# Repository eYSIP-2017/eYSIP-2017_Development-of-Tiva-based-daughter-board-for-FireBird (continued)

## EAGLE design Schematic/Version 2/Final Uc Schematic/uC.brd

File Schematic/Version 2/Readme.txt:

The version 2 of uC based board is not routed. The sechmatic is changed as per requirement. The components are placed in their respective postions. 
Only the routing part is left.

The version 2 of Plug and Play board is fully completed.

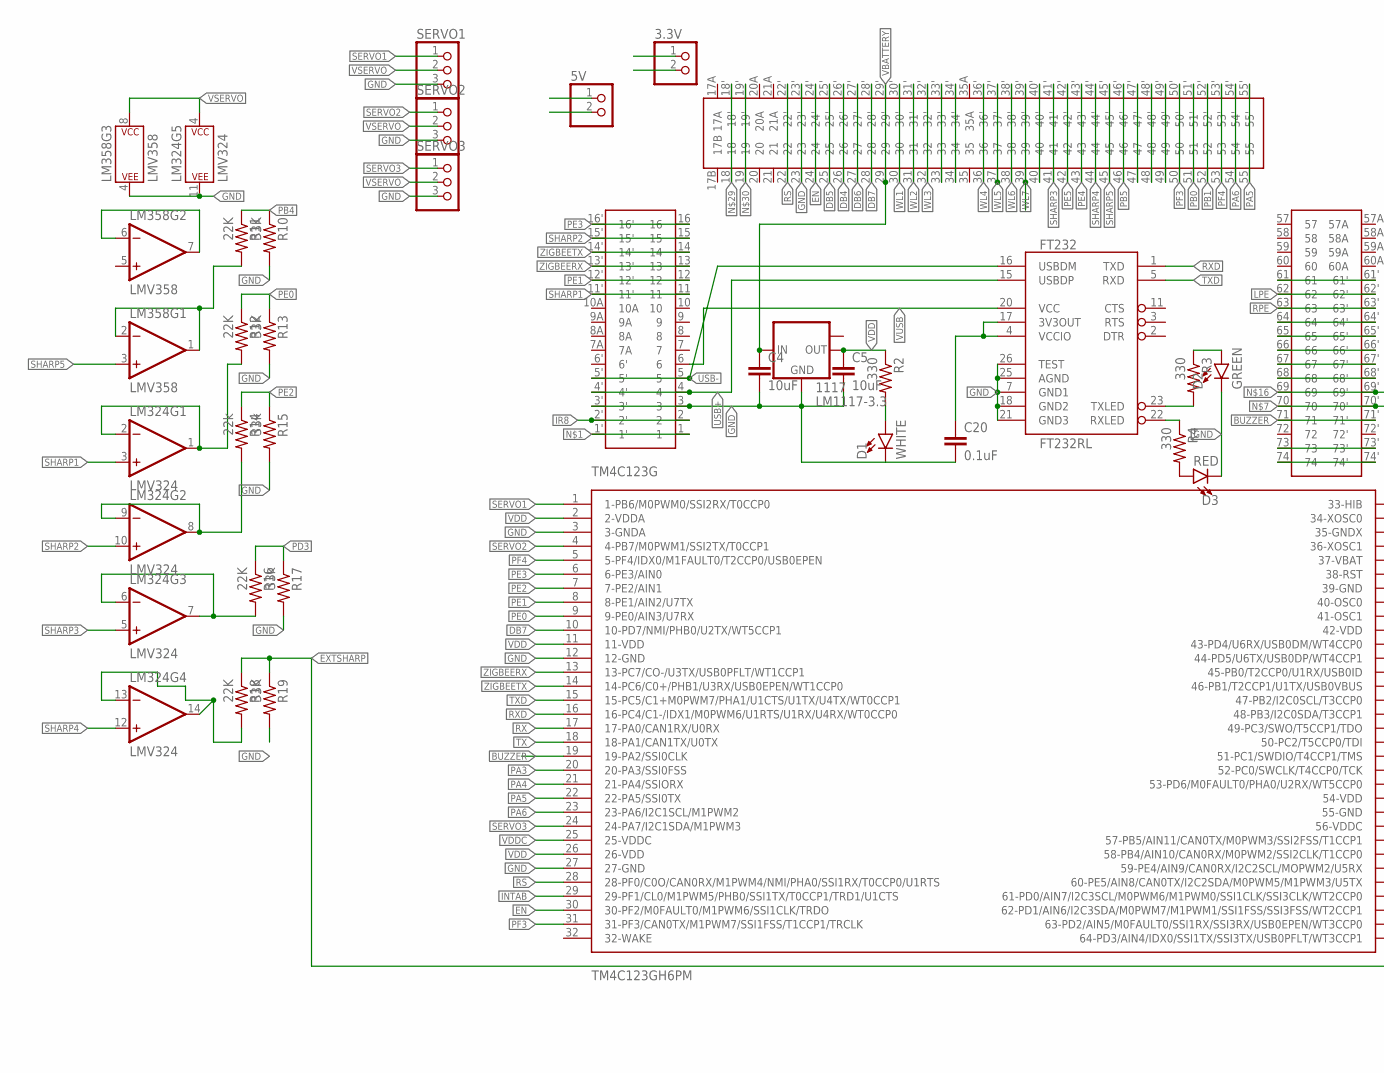
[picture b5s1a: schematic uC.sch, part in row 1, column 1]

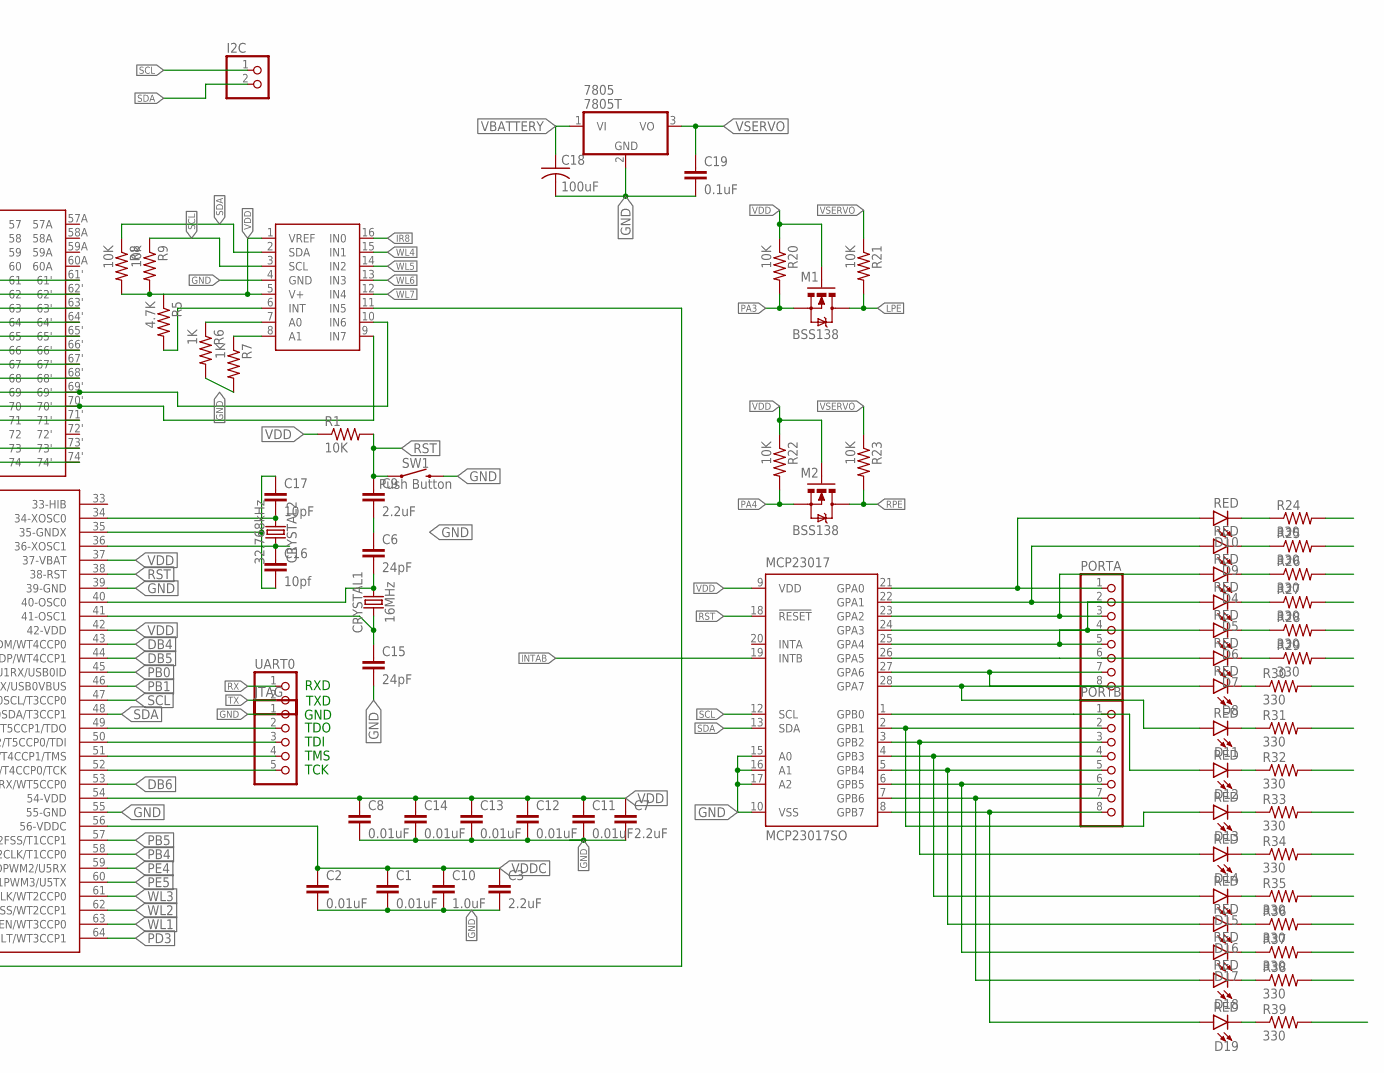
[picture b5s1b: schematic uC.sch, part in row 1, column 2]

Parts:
3.3V, 5V: PINHD-1X2; 1X02
1117: LM1117-3.3; SOT223
7805: 7805T; TO220H
ADC128D818: ADC128D818; ADC12_SD
C1, C2, C8, C11, C12, C13, C14: 0.01uF; 1206
C3, C7, C9: 2.2uF; 1206
C4, C5: 10uF; 1206
C6, C15: 24pF; 1206
C10: 1.0uF; 1206
C16: 10pf; 1206
C17: 10pF; 1206
C18: 100uF; C025-024X044
C19, C20: 0.1uF; 1206
CRYSTAL1: 16MHz; HC49US
CRYSTAL2: 32.768kHz; CRYSTAL-PTH-2X6-CYL
D1: WHITE; LED-1206
D2: GREEN; LED-1206
D3, D4, D5, D6, D7, D8, D9, D10, D11, D12, D13, D14, D15, D16, D17, D18, D19: RED; LED-1206
FT232: FT232RL; SSOP28DB
I2C: PINHD-1X2; 1X02
JTAG: PINHD-1X5_2.54; 1X05
LM324: LMV324; SO14
LM358: LMV358; SO08
M1, M2: BSS138; SOT23-3
MCP23017: MCP23017SO; SO28W
PORTA: PINHD-1X8BIG; 1X08-BIG
PORTB: PINHD-1X8BIG; 1X08-BIG
R1, R8: 10K; M1206
R2, R3, R4, R24, R25, R26, R27, R28, R29, R30, R31, R32, R33, R34, R35, R36, R37, R38, R39: 330; M1206
R5: 4.7K; M1206
R6, R7: 1K; M1206
R9: 10k; M1206
R10, R13, R19: 33K; M1206
R11, R12, R16, R18: 22K; M1206
R14: 22k; M1206
R15, R17: 33k; M1206
R20, R21, R22, R23: 10K; 1206
SERVO1, SERVO2, SERVO3: PINHD-1X3; 1X03
SW1: Push Button; TACTILE_SWITCH_PTH_6.0MM
TM4C123G: TM4C123GH6PM; LQFP
U$1: DAUGHTERBOARDDAUGHTERBOARD; DAUGHTERBOARD
UART0: PINHD-1X2; 1X02

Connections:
BUZZER: TM4C123G.19 (19-PA2/SSI0CLK), U$1.71, U$1.71'
DB4: TM4C123G.43 (43-PD4/U6RX/USB0DM/WT4CCP0), U$1.26, U$1.26'
DB5: TM4C123G.44 (44-PD5/U6TX/USB0DP/WT4CCP1), U$1.25, U$1.25'
DB6: TM4C123G.53 (53-PD6/M0FAULT0/PHA0/U2RX/WT5CCP0), U$1.27, U$1.27'
DB7: TM4C123G.10 (10-PD7/NMI/PHB0/U2TX/WT5CCP1), U$1.28, U$1.28'
EN: TM4C123G.30 (30-PF2/M0FAULT0/M1PWM6/SSI1CLK/TRDO), U$1.24, U$1.24'
EXTSHARP: ADC128D818.11 (IN5), R18.1, R19.1
FDSFSDF: LM324.1 (OUT), LM324.2 (-IN), R12.2
GND: 3.3V.2, 5V.2, 1117.1 (GND), 7805.2 (GND), ADC128D818.4 (GND), C1.2, C2.2, C3.2, C4.2, C5.2, C6.1, C7.2, C8.2, C9.2, C10.2, C11.2, C12.2, C13.2, C14.2, C15.2, C18.2, C19.2, C20.2, D1.C, D2.C, D3.C, FT232.7 (GND1), FT232.18 (GND2), FT232.21 (GND3), FT232.25 (AGND), FT232.26 (TEST), JTAG.1, LM324.11 (P$V-), LM358.4 (P$V-), MCP23017.10 (VSS), MCP23017.15 (A0), MCP23017.16 (A1), MCP23017.17 (A2), R6.2, R7.2, R10.2, R13.2, R15.2, R17.2, R19.2, R24.2, R25.2, R26.2, R27.2, R28.2, R29.2, R30.2, R31.2, R32.2, R33.2, R34.2, R35.2, R36.2, R37.2, R38.2, R39.2, SERVO1.3, SERVO2.3, SERVO3.3, SW1.3 (2), TM4C123G.3 (3-GNDA), TM4C123G.12 (12-GND), TM4C123G.27 (27-GND), TM4C123G.39 (39-GND), TM4C123G.55 (55-GND), U$1.3, U$1.3', U$1.23, U$1.23'
GNDX: C16.2, C17.1, TM4C123G.35 (35-GNDX)
HGHJ: LM358.1 (OUT), LM358.2 (-IN), R11.2
INTAB: MCP23017.19 (INTB), TM4C123G.29 (29-PF1/CL0/M1PWM5/PHB0/SSI1TX/T0CCP1/TR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)
IR8: ADC128D818.16 (IN0), U$1.2, U$1.2'
LPE: M1.3 (D), R21.2, U$1.62, U$1.62'
unnamed: U$1.1, U$1.1'
unnamed: D10.A, MCP23017.21 (GPA0), PORTA.1
unnamed: C6.2, CRYSTAL1.2, TM4C123G.40 (40-OSC0)
unnamed: D9.A, MCP23017.22 (GPA1), PORTA.2
unnamed: LM358.6 (-IN), LM358.7 (OUT)
unnamed: ADC128D818.9 (IN7), U$1.70, U$1.70'
unnamed: D4.A, MCP23017.23 (GPA2), PORTA.3
unnamed: D5.A, MCP23017.24 (GPA3), PORTA.4
unnamed: D6.A, MCP23017.25 (GPA4), PORTA.5
unnamed: JTAG.5, TM4C123G.52 (52-PC0/SWCLK/T4CCP0/TCK)
unnamed: U$1.74, U$1.74'
unnamed: U$1.73, U$1.73'
unnamed: LM324.13 (-IN), LM324.14 (OUT), R18.2
unnamed: JTAG.4, TM4C123G.51 (51-PC1/SWDIO/T4CCP1/TMS)
unnamed: ADC128D818.10 (IN6), D10.C, R24.1, U$1.69, U$1.69'
unnamed: U$1.68, U$1.68'
unnamed: U$1.67, U$1.67'
unnamed: U$1.66, U$1.66'
unnamed: U$1.65, U$1.65'
unnamed: U$1.64, U$1.64'
unnamed: ADC128D818.7 (A0), R6.1
unnamed: D7.A, MCP23017.26 (GPA5), PORTA.6
unnamed: U$1.61, U$1.61'
unnamed: JTAG.3, TM4C123G.50 (50-PC2/T5CCP0/TDI)
unnamed: D1.A, R2.2
unnamed: C17.2, CRYSTAL2.1, TM4C123G.34 (34-XOSC0)
unnamed: C16.1, CRYSTAL2.2, TM4C123G.36 (36-XOSC1)
unnamed: D9.C, R25.1, U$1.18, U$1.18'
unnamed: D4.C, R26.1, U$1.19, U$1.19'
unnamed: JTAG.2, TM4C123G.49 (49-PC3/SWO/T5CCP1/TDO)
unnamed: D8.A, MCP23017.27 (GPA6), PORTA.7
unnamed: D11.A, MCP23017.28 (GPA7), PORTA.8
unnamed: D12.A, MCP23017.1 (GPB0), PORTB.1
unnamed: D13.A, MCP23017.2 (GPB1), PORTB.2
unnamed: D14.A, MCP23017.3 (GPB2), PORTB.3
unnamed: D15.A, MCP23017.4 (GPB3), PORTB.4
unnamed: D16.A, MCP23017.5 (GPB4), PORTB.5
unnamed: D17.A, MCP23017.6 (GPB5), PORTB.6
unnamed: D18.A, MCP23017.7 (GPB6), PORTB.7
unnamed: D19.A, MCP23017.8 (GPB7), PORTB.8
unnamed: U$1.33, U$1.33'
unnamed: U$1.34, U$1.34'
unnamed: D5.C, R27.1
unnamed: D6.C, R28.1
unnamed: D7.C, R29.1
unnamed: D8.C, R30.1
unnamed: U$1.40, U$1.40'
unnamed: D11.C, R31.1
unnamed: D12.C, R32.1
unnamed: D13.C, R33.1
unnamed: D19.C, R39.1
unnamed: D18.C, R38.1
unnamed: D17.C, R37.1
unnamed: U$1.47, U$1.47'
unnamed: U$1.48, U$1.48'
unnamed: U$1.49, U$1.49'
unnamed: D16.C, R36.1
unnamed: D15.C, R35.1
unnamed: D14.C, R34.1
unnamed: FT232.22 (RXLED), R4.1
unnamed: FT232.23 (TXLED), R3.2
unnamed: D3.A, R4.2
unnamed: D2.A, R3.1
unnamed: ADC128D818.6 (INT), R5.2
unnamed: ADC128D818.8 (A1), R7.1
unnamed: C20.1, FT232.4 (VCCIO), FT232.17 (3V3OUT)
NO: C15.1, CRYSTAL1.1, TM4C123G.41 (41-OSC1)
PA3: M1.2 (S), R20.2, TM4C123G.20 (20-PA3/SSI0FSS)
PA4: M2.2 (S), R22.2, TM4C123G.21 (21-PA4/SSIORX)
PA5: TM4C123G.22 (22-PA5/SSI0TX), U$1.55, U$1.55'
PA6: TM4C123G.23 (23-PA6/I2C1SCL/M1PWM2), U$1.54, U$1.54'
PB0: TM4C123G.45 (45-PB0/T2CCP0/U1RX/USB0ID), U$1.51, U$1.51'
PB1: TM4C123G.46 (46-PB1/T2CCP1/U1TX/USB0VBUS), U$1.52, U$1.52'
PB4: R10.1, R11.1, TM4C123G.58 (58-PB4/AIN10/CAN0RX/M0PWM2/SSI2CLK/T1CC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)
PB5: TM4C123G.57 (57-PB5/AIN11/CAN0TX/M0PWM3/SSI2FSS/T1CC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), U$1.46, U$1.46'
PD3: R16.1, R17.1, TM4C123G.64 (64-PD3/AIN4/IDX0/SSI1TX/SSI3TX/USB0PFLT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)
PE0: R12.1, R13.1, TM4C123G.9 (9-PE0/AIN3/U7RX)
PE1: TM4C123G.8 (8-PE1/AIN2/U7TX), U$1.12, U$1.12'
PE2: R14.1, R15.1, TM4C123G.7 (7-PE2/AIN1)
PE3: TM4C123G.6 (6-PE3/AIN0), U$1.16, U$1.16'
PE4: TM4C123G.59 (59-PE4/AIN9/CAN0RX/I2C2SCL/MOPWM2/U5RX), U$1.43, U$1.43'
PE5: TM4C123G.60 (60-PE5/AIN8/CAN0TX/I2C2SDA/M0PWM5/M1PWM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), U$1.42, U$1.42'
PF3: TM4C123G.31 (31-PF3/CAN0TX/M1PWM7/SSI1FSS/T1CCP1/TRC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), U$1.50, U$1.50'
PF4: TM4C123G.5 (5-PF4/IDX0/M1FAULT0/T2CCP0/USB0EPEN), U$1.53, U$1.53'
RPE: M2.3 (D), R23.2, U$1.63, U$1.63'
RS: TM4C123G.28 (28-PF0/C0O/CAN0RX/M1PWM4/NMI/PHA0/SSI1R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), U$1.22, U$1.22'
RST: C9.1, MCP23017.18 (!RESET), R1.2, SW1.1, TM4C123G.38 (38-RST)
RX: TM4C123G.17 (17-PA0/CAN1RX/U0RX), UART0.1
RXD: FT232.1 (TXD), TM4C123G.16 (16-PC4/C1-/IDX1/M0PWM6/U1RTS/U1RX/U4RX/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)
SCL: ADC128D818.3 (SCL), I2C.1, MCP23017.12 (SCL), R9.1, TM4C123G.47 (47-PB2/I2C0SCL/T3CCP0)
SDA: ADC128D818.2 (SDA), I2C.2, MCP23017.13 (SDA), R8.1, TM4C123G.48 (48-PB3/I2C0SDA/T3CCP1)
SDFSDFSD: LM324.8 (OUT), LM324.9 (-IN), R14.2
SERVO1: SERVO1.1, TM4C123G.1 (1-PB6/M0PWM0/SSI2RX/T0CCP0)
SERVO2: SERVO2.1, TM4C123G.4 (4-PB7/M0PWM1/SSI2TX/T0CCP1)
SERVO3: SERVO3.1, TM4C123G.24 (24-PA7/I2C1SDA/M1PWM3)
SHARP1: LM324.3 (+IN), U$1.11, U$1.11'
SHARP2: LM324.10 (+IN), U$1.15, U$1.15'
SHARP3: LM324.5 (+IN), U$1.41, U$1.41'
SHARP4: LM324.12 (+IN), U$1.44, U$1.44'
SHARP5: LM358.3 (+IN), U$1.45, U$1.45'
TX: TM4C123G.18 (18-PA1/CAN1TX/U0TX), UART0.2
TXD: FT232.5 (RXD), TM4C123G.15 (15-PC5/C1+M0PWM7/PHA1/U1CTS/U1TX/U4TX/W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)
USB+: FT232.15 (USBDP), U$1.4, U$1.4'
USB-: FT232.16 (USBDM), U$1.5, U$1.5'
VBATTERY: 1117.3 (IN), 7805.1 (VI), C4.1, C18.1, U$1.29, U$1.29'
VDD: 3.3V.1, 1117.2 (OUT), ADC128D818.1 (VREF), ADC128D818.5 (V+), C5.1, C7.1, C8.1, C11.1, C12.1, C13.1, C14.1, M1.1 (G), M2.1 (G), MCP23017.9 (VDD), R1.1, R2.1, R5.1, R8.2, R9.2, R20.1, R22.1, TM4C123G.2 (2-VDDA), TM4C123G.11 (11-VDD), TM4C123G.26 (26-VDD), TM4C123G.37 (37-VBAT), TM4C123G.42 (42-VDD), TM4C123G.54 (54-VDD)
VDDC: C1.1, C2.1, C3.1, C10.1, TM4C123G.25 (25-VDDC), TM4C123G.56 (56-VDDC)
VSERVO: 5V.1, 7805.3 (VO), C19.1, LM324.4 (P$V+), LM358.8 (P$V+), R21.1, R23.1, SERVO1.2, SERVO2.2, SERVO3.2
VUSB: FT232.20 (VCC), U$1.6
WL1: TM4C123G.63 (63-PD2/AIN5/M0FAULT0/SSI1RX/SSI3RX/USB0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), U$1.30, U$1.30'
WL2: TM4C123G.62 (62-PD1/AIN6/I2C3SDA/M0PWM7/M1PWM1/SSI1F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), U$1.31, U$1.31'
WL3: TM4C123G.61 (61-PD0/AIN7/I2C3SCL/M0PWM6/M1PWM0/SSI1C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), U$1.32, U$1.32'
WL4: ADC128D818.15 (IN1), U$1.36, U$1.36'
WL5: ADC128D818.14 (IN2), U$1.37, U$1.37'
WL6: ADC128D818.13 (IN3), U$1.38, U$1.38'
WL7: ADC128D818.12 (IN4), U$1.39, U$1.39'
XXVX: LM324.6 (-IN), LM324.7 (OUT), R16.2
ZIGBEERX: TM4C123G.13 (13-PC7/CO-/U3TX/USB0PFLT/WT1CCP1), U$1.13, U$1.13'
ZIGBEETX: TM4C123G.14 (14-PC6/C0+/PHB1/U3RX/USB0EPEN/WT1CCP0), U$1.14, U$1.14'

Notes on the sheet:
TCK
TMS
TDI
TDO
TXD
RXD
GND

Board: 2 copper layers, 102 parts (37 on the bottom side), 133 nets, no tracks yet.

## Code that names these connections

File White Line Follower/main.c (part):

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
ADC Connection:
          CH       PORT    Sensor
           2       PE1     White line sensor 3
           1       PE2     White line sensor 2
           0       PE3     White line sensor 1
          11       PB5     IR Proximity analog sensor 1
           7       PD5     IR Proximity analog sensor 2
           4       PD3     IR Proximity analog sensor 3
           6       PD1     IR Proximity analog sensor 4
           8       PE5     IR Proximity analog sensor 5
           3       PE0     IR Proximity analog sensor 7
          10       PB4     Sharp IR range sensor 1
           5       PD2     Sharp IR range sensor 3
           9       PE4     Sharp IR range sensor 5
LCD Connection:
             LCD      Board Pins
              RS  --> PD6
              RW  --> GND
              EN  --> PD7
              DB7 --> PA5
              DB6 --> PA4
              DB5 --> PA3
              DB4 --> PA2
Motor Connection:
                L-1---->PF3;        L-2---->PB3;
                R-1---->PC4;        R-2---->PC6;
                PF2----> PWM L     PC5----> PWM R;

****************************************************************************************************/
#include <stdint.h>
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 * Macros have been defined at starting
 * Macros for directions are 8 bits
 * Out of these 8 bits only 4 are used
 * Bit 0 (LSB) corresponds to PB3
 * Bit 3       corresponds to PF3
 * Bit 4       corresponds to PC4
 * Bit 6       corresponds to PF6
 *****************************************************/
void motion(uint8_t direction){
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
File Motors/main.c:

/********************************************************************************
 Written by: Ayush Gaurav

 Date: 29th May 2017

This experiment demonstrates simple motion control.

 Concepts covered: Simple motion control

 There are two components to the motion control:
 1. Direction control using pins PORTA0 to PORTA3
 2. Velocity control by PWM on pins PA4 and PA5 using OC5A and OC5B of timer 5.

 In this experiment for the simplicity PL3 and PL4 are kept at logic 1.

 Pins for PWM are kept at logic 1.

 Connection Details:    L-1---->PB0;        L-2---->PB1;
                        R-1---->PB2;        R-2---->PB3;
                        PB4 ----> PWM L  PB5----> PWM R;


*********************************************************************************/
#include <stdint.h>
#include <stdbool.h>
#include "inc/hw_types.h"
#include "inc/hw_memmap.h"
//This header File is important to Unlock GPIO Pins
#include "inc/hw_gpio.h"
#include "driverlib/sysctl.h"
#include "driverlib/gpio.h"
#define motorPort       GPIO_PORTB_BASE
#define leftMotor1      GPIO_PIN_0
#define leftMotor2      GPIO_PIN_1
#define leftMotorPWM    GPIO_PIN_4
#define rightMotor1     GPIO_PIN_2
#define rightMotor2     GPIO_PIN_3
#define rightMotorPWM   GPIO_PIN_5
#define right           0x3A
#define left            0x35
#define forward         0x36
#define backward        0x39
#define stop            0x30
void setupCLK();
void peripheralEnable();
void configIOPin();
void delay_ms(uint64_t delay);
void delay_ms(uint64_t delay);
void motion(uint8_t);
int main(void) {
    setupCLK();
    peripheralEnable();
    configIOPin();
    while(1){
        motion(forward);
        delay_ms(1000);
        motion(right);
        delay_ms(1000);
        motion(left);
        delay_ms(1000);
        motion(backward);
        delay_ms(1000);
    }
}
/***************************************************************************************
 * This function is used to setup Clock frequency of the controller
 * It can be changed through codes
 * In this we have set frequency as 40Mhz
 * Frequency is set by SYSDIV which can be found in data sheet for different frequencies
 ***************************************************************************************/
void setupCLK(){
    SysCtlClockSet(SYSCTL_SYSDIV_5|SYSCTL_USE_PLL|SYSCTL_XTAL_16MHZ|SYSCTL_OSC_MAIN);
}
/*******************************
 * Enabling System Peripherals
 * PORTF in this case
 * PF1 for buzzer output
 ******************************/
void peripheralEnable(){
    SysCtlPeripheralEnable(SYSCTL_PERIPH_GPIOB);
}
/*************************************
 * Configuring Pin as Input Or Output
 *************************************/
void configIOPin(){
    GPIOPinTypeGPIOOutput(motorPort,rightMotor1|rightMotor2|rightMotorPWM|leftMotorPWM|leftMotor1|leftMotor2);
}
/*************************************
 * Calculating Delays
 *************************************/
void delay_ms(uint64_t delay){
    SysCtlDelay(delay*(SysCtlClockGet()/3000));
}
void delay_us(uint64_t delay){
    SysCtlDelay(delay*(SysCtlClockGet()/3000000UL));
}
void motion(uint8_t direction){
    GPIOPinWrite(motorPort,rightMotor1|rightMotor2|rightMotorPWM|leftMotorPWM|leftMotor1|leftMotor2,direction);
}

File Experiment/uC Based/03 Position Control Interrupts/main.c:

/*********************************************************************************
 Written by: Ayush Gaurav and Nagesh K.
From ERTS Lab, CSE Department, IIT Bombay.

 Date: 16th June 2017

 This experiment demonstrates use of position encoders present on both the wheels.

 Concepts covered: External Interrupts, Position control

 Microcontroller pins used:
 L-1---->PB0;        L-2---->PB1;
 R-1---->PF4;        R-2---->PA5;
 PF3----> PWM L     PA6----> PWM R;
 PA4 : External interrupt for left motor position encoder
 PA3 : External interrupt for the right position encoder
**********************************************************************************/

#include <stdint.h>
#include <stdbool.h>
#include "inc/tm4c123gh6pm.h"
#include "inc/hw_memmap.h"
#include "inc/hw_types.h"
#include "inc/hw_gpio.h"
#include "driverlib/sysctl.h"
#include "driverlib/interrupt.h"
#include "driverlib/gpio.h"
#define right           0x22
#define left            0x11
#define softRight       0x02
#define softLeft        0x10
#define forward         0x12
#define backward        0x21
#define stop            0x00
void setupCLK();
void peripheralEnable();
void gpioEnable();
void interruptEnable();
void encoderInterruptEncountered();
void linearDistanceMM(unsigned int);
void angleRotate(uint16_t);
void forwardMM(unsigned int);
void backwardMM(unsigned int);
void leftDegrees(unsigned int);
void rightDegrees(unsigned int);
void delay_ms(uint64_t delay);
void delay_us(uint64_t delay);
void motion(uint8_t direction);
volatile uint16_t ShaftCountRight=0,ShaftCountLeft=0;
int main(void) {
    setupCLK();
    peripheralEnable();
    gpioEnable();
    interruptEnable();
    while(1){
        forwardMM(100);
        delay_ms(1000);
        rightDegrees(90);
        delay_ms(1000);
}
}

/***************************************************************************************
 * This function is used to setup Clock frequency of the controller
 * It can be changed through codes
 * In this we have set frequency as 40Mhz
 * Frequency is set by SYSDIV which can be found in data sheet for different frequencies
 ***************************************************************************************/
void setupCLK(){
    SysCtlClockSet(SYSCTL_SYSDIV_5|SYSCTL_USE_PLL|SYSCTL_XTAL_16MHZ|SYSCTL_OSC_MAIN);
}

/*******************************
 * Enabling System Peripherals
 * PORTF,PORTB and PORTA in this case
 ******************************/
void peripheralEnable(){
    SysCtlPeripheralEnable(SYSCTL_PERIPH_GPIOB);
    SysCtlPeripheralEnable(SYSCTL_PERIPH_GPIOF);
    SysCtlPeripheralEnable(SYSCTL_PERIPH_GPIOA);
}

/*************************************
 * Configuring Pin as Input Or Output
 * Setting PWM Pins to Always High
 * Weak Pull to the Input Pins
 *************************************/
void gpioEnable(){
    GPIOPinTypeGPIOOutput(GPIO_PORTF_BASE,GPIO_PIN_1|GPIO_PIN_2);
    GPIOPinTypeGPIOOutput(GPIO_PORTB_BASE,GPIO_PIN_0|GPIO_PIN_1);
    GPIOPinTypeGPIOOutput(GPIO_PORTA_BASE,GPIO_PIN_6|GPIO_PIN_5);
    GPIOPinTypeGPIOOutput(GPIO_PORTF_BASE,GPIO_PIN_4|GPIO_PIN_3);
    GPIOPinWrite(GPIO_PORTF_BASE,GPIO_PIN_3,255);
    GPIOPinWrite(GPIO_PORTA_BASE,GPIO_PIN_6,255);
    GPIOPinTypeGPIOInput(GPIO_PORTA_BASE, GPIO_PIN_4|GPIO_PIN_3);
    GPIOPadConfigSet(GPIO_PORTA_BASE ,GPIO_PIN_4|GPIO_PIN_5,GPIO_STRENGTH_2MA,GPIO_PIN_TYPE_STD_WPU);
}
/****For Enabling Interrupt on PortA****/
void interruptEnable(){
    GPIOIntDisable(GPIO_PORTA_BASE,GPIO_PIN_4|GPIO_PIN_3);
    GPIOIntClear(GPIO_PORTA_BASE, GPIO_PIN_4|GPIO_PIN_3);
    GPIOIntRegister(GPIO_PORTA_BASE, encoderInterruptEncountered);
    GPIOIntTypeSet(GPIO_PORTA_BASE,GPIO_PIN_4|GPIO_PIN_3,GPIO_FALLING_EDGE);
    GPIOIntEnable(GPIO_PORTA_BASE,GPIO_PIN_4|GPIO_PIN_3);
}
/**** ISR For External Interrupt on PortA************************
 * Check on which pin of the PORTA has encountered an interrupt
 * There is only one ISR for complete PORT
 * No two PORTs can have same ISR
 ****************************************************************/
void encoderInterruptEncountered(){
   if(GPIOIntStatus(GPIO_PORTA_BASE, false)&GPIO_PIN_4){
       ShaftCountLeft++;
       GPIOIntClear(GPIO_PORTA_BASE, GPIO_PIN_4);
   }
   if(GPIOIntStatus(GPIO_PORTA_BASE, false)&GPIO_PIN_3){
       ShaftCountRight++;
       GPIOIntClear(GPIO_PORTA_BASE, GPIO_PIN_3);
   }
}
/*************************************
 * Calculating Delays
 *************************************/
void delay_ms(uint64_t delay){
    SysCtlDelay(delay*(SysCtlClockGet()/3000));
}
void delay_us(uint64_t delay){
    SysCtlDelay(delay*(SysCtlClockGet()/3000000UL));
}
/******************************************************
 * This function is for giving the direction of motion
 * Macros have been defined at starting
 * Macros for directions are 8 bits
 * Out of these 8 bits only 4 are used
 * Bit 0 (LSB) corresponds to PB3
 * Bit 3       corresponds to PF3
 * Bit 4       corresponds to PC4
 * Bit 6       corresponds to PF6
 *****************************************************/
void motion(uint8_t direction){
    GPIOPinWrite(GPIO_PORTB_BASE,GPIO_PIN_0|GPIO_PIN_1,direction);
    GPIOPinWrite(GPIO_PORTA_BASE,GPIO_PIN_5,direction);
    GPIOPinWrite(GPIO_PORTF_BASE,GPIO_PIN_4,direction);
}
/****************************************************
 * Function to Rotate to desired Angle
 * Resolution can be Change to Get Higher Precision
 ****************************************************/
void angleRotate(uint16_t Degrees){
     unsigned long int ReqdShaftCountInt = 0;  // division by resolution to get shaft count
     ReqdShaftCountInt = Degrees/ 4.09;;
     ShaftCountRight = 0;
     ShaftCountLeft = 0;
     while (1){
         if((ShaftCountRight>=ReqdShaftCountInt)&&(ShaftCountLeft>=ReqdShaftCountInt))
             break;
     }
     motion(stop);
}
/****************************************************
 * Function to Move in a Linear Distance
 * Resolution can be Change to Get Higher Precision
 ****************************************************/
void linearDistanceMM(unsigned int DistanceInMM){
     unsigned long int ReqdShaftCountInt = 0;
     ReqdShaftCountInt =DistanceInMM / 5.338;;
     ShaftCountRight=0;
     ShaftCountLeft=0;
     while(1){
         if((ShaftCountRight > ReqdShaftCountInt)&&(ShaftCountLeft > ReqdShaftCountInt))
             break;
         else if((ShaftCountRight > ReqdShaftCountInt))
             motion(softRight);
         else if((ShaftCountLeft > ReqdShaftCountInt))
             motion(softLeft);
     }
     motion(stop); //Stop robot
}
void forwardMM(unsigned int DistanceInMM){
    motion(forward);
     linearDistanceMM(DistanceInMM);
}

void backwardMM(unsigned int DistanceInMM){
    motion(backward);
    linearDistanceMM(DistanceInMM);
}
void leftDegrees(unsigned int Degrees){
    motion(left); //Turn left
    angleRotate(Degrees);
}
void rightDegrees(unsigned int Degrees){
    motion(right); //Turn right
     angleRotate(Degrees);
}

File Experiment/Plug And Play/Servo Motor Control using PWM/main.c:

/********************************************************************************
 Written by: Ayush Gaurav and Nagesh K.
From eRTS Lab, CSE Department, IIT Bombay.

 Date: 16th June 2017

This experiment demonstrates position control of Servo Motors.

 Concepts covered: Postion Control using PWM.

Note: Refer the hardware manual to identify the ground pin.

 Connection Details:
            For Plug And Play Board
                        Servo1 ------> PF1
                        Servo2 ------> PB6
                        Servo3 ------> PB7

*********************************************************************************/
#include <stdint.h>
#include <stdbool.h>
#include "inc/hw_types.h"
#include "inc/hw_memmap.h"
#include "driverlib/pin_map.h"
//This header File is important to Unlock GPIO Pins
#include "inc/hw_gpio.h"
#include "driverlib/sysctl.h"
#include "driverlib/gpio.h"
//Used for PWM
#include "driverlib/pwm.h"

#define PWM_FREQUENCY  55

volatile uint32_t ui32Load;
volatile uint32_t ui32PWMClock;
volatile uint8_t ui8Adjust;

void setupCLK();
void peripheralEnable();
void delay_ms(uint64_t delay);
void delay_ms(uint64_t delay);
void enablePWM();

int main(void){
    void setupCLK();
    void peripheralEnable();
    void delay_ms(uint64_t delay);
    void delay_ms(uint64_t delay);
    void enablePWM();
    while(1){
        for(ui8Adjust = 56;ui8Adjust < 111; ui8Adjust ++){
            PWMPulseWidthSet(PWM1_BASE, PWM_OUT_5, ui8Adjust * ui32Load / 1000);
            PWMPulseWidthSet(PWM0_BASE, PWM_OUT_0, ui8Adjust * ui32Load / 1000);
            PWMPulseWidthSet(PWM0_BASE, PWM_OUT_1, ui8Adjust * ui32Load / 1000);
            delay_ms(50);
        }
    }
}

/***************************************************************************************
 * This function is used to setup Clock frequency of the controller
 * It can be changed through codes
 * In this we have set frequency as 40Mhz
 * Frequency is set by SYSDIV which can be found in data sheet for different frequencies
 * * The PWM module is clocked by the system clock through a divider, and that divider has
   a range of 2 to 64.
 * By setting the divider to 64, it will run the PWM clock at 625 kHz.
 ***************************************************************************************/
void setupCLK(){
    SysCtlClockSet(SYSCTL_SYSDIV_5|SYSCTL_USE_PLL|SYSCTL_XTAL_16MHZ|SYSCTL_OSC_MAIN);
    SysCtlPWMClockSet(SYSCTL_PWMDIV_64);    //625kHz PWM Clock
}
/*******************************
 * Enabling System Peripherals
 * PORTF,PORTB and PORTC in this case
 ******************************/
void peripheralEnable(){
    SysCtlPeripheralEnable(SYSCTL_PERIPH_GPIOB);
    SysCtlPeripheralEnable(SYSCTL_PERIPH_GPIOF);
    SysCtlPeripheralEnable(SYSCTL_PERIPH_PWM0); // Enabling PWM0
    SysCtlPeripheralEnable(SYSCTL_PERIPH_PWM1); // Enabling PWM1
}
/*************************************
 * Calculating Delays
 *************************************/
void delay_ms(uint64_t delay){
    SysCtlDelay(delay*(SysCtlClockGet()/3000));
}
void delay_us(uint64_t delay){
    SysCtlDelay(delay*(SysCtlClockGet()/3000000UL));
}
/******************************************************
 * This function is for enabling the PWM Modules
 * PWM can be enabled on a pin based on the datasheet
 *****************************************************/
void enablePWM(){
    GPIOPinTypePWM(GPIO_PORTF_BASE, GPIO_PIN_1);
    GPIOPinConfigure(GPIO_PF1_M1PWM5);
    GPIOPinTypePWM(GPIO_PORTB_BASE, GPIO_PIN_6);
    GPIOPinConfigure(GPIO_PB6_M0PWM0);
    GPIOPinTypePWM(GPIO_PORTB_BASE, GPIO_PIN_7);
    GPIOPinConfigure(GPIO_PB7_M0PWM1);

    ui32PWMClock = SysCtlClockGet() / 64;   //Divide the system clock by 64 to get the PWM frequency
    ui32Load = (ui32PWMClock / PWM_FREQUENCY) - 1;  //Calculate the number of counts required for 55Hz

    PWMGenConfigure(PWM0_BASE, PWM_GEN_0, PWM_GEN_MODE_DOWN);//Count Down Mode
    PWMGenPeriodSet(PWM0_BASE, PWM_GEN_0, ui32Load); //Load Count value
    PWMGenConfigure(PWM1_BASE, PWM_GEN_2, PWM_GEN_MODE_DOWN);//Count Down Mode
    PWMGenPeriodSet(PWM1_BASE, PWM_GEN_2, ui32Load); //Load Count value
    PWMGenEnable(PWM0_BASE, PWM_GEN_0);
    PWMGenEnable(PWM1_BASE, PWM_GEN_2);
    PWMOutputState(PWM1_BASE, PWM_OUT_5_BIT, true);
    PWMOutputState(PWM0_BASE, PWM_OUT_0_BIT, true);
    PWMOutputState(PWM0_BASE, PWM_OUT_1_BIT, true);
}

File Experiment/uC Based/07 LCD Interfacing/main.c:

/*****************************************************************************************
 Written by: Ayush Gaurav And Nagesh K.
 From ERTS Lab, CSE Department, IIT Bombay.

 Date: 16th June 2017

 This experiment demonstrates LCD interfacing in 4 bit mode

 Concepts covered:  LCD interfacing

Connections:
               uC based board
             LCD      Board Pins
              RS  --> PF0
              RW  --> GND
              EN  --> PF2
              DB7 --> PD7
              DB6 --> PD6
              DB5 --> PD5
              DB4 --> PD4

 Note: Make sure that in the configuration options following settings are
 done for proper operation of the code.
*****************************************************************************************/
#include <stdint.h>
#include <stdbool.h>
#include "inc/hw_types.h"
#include "inc/hw_memmap.h"
#include "inc/hw_gpio.h" //To unlock locked pins for GPIO
#include "driverlib/sysctl.h"
#include "driverlib/gpio.h"
#include<math.h>
#include<stdlib.h>
#ifndef     lcdPORT
#define     lcdPORT     GPIO_PORTF_BASE
#endif
#ifndef     lcdDDR
#define     lcdDDR      GPIO_PORTD_BASE
#endif
#ifndef     RS
#define     RS          GPIO_PIN_0
#endif
#ifndef     EN
#define     EN          GPIO_PIN_2
#endif
#ifndef     D4
#define     D4          GPIO_PIN_4
#endif
#ifndef     D5
#define     D5          GPIO_PIN_5
#endif
#ifndef     D6
#define     D6          GPIO_PIN_6
#endif
#ifndef     D7
#define     D7          GPIO_PIN_7
#endif
#define LOCK_F (*((volatile unsigned long *)0x40025520))
#define CR_F   (*((volatile unsigned long *)0x40025524))
unsigned char cursorPositionCheck=0;
void lcdInit();
void lcdCommand(unsigned char);
void lcdData(unsigned char);
void lcdString(char*);
void lcdGotoxy(unsigned char,unsigned char);
void lcdClear();
void lcdCheck();
void setupCLK();
void peripheralEnable();
void configIOPin();
void _delay_ms(uint64_t delay);
void _delay_us(uint64_t delay);
int main(){
    setupCLK();
    peripheralEnable();
    configIOPin();
    lcdInit();
    lcdClear();
    lcdGotoxy(0,0);
    lcdString("TIVA C Series");
    while(1){
    }
}
/***************************************************************************************
 * This function is used to setup Clock frequency of the controller
 * It can be changed through codes
 * In this we have set frequency as 40Mhz
 * Frequency is set by SYSDIV which can be found in data sheet for different frequencies
 ***************************************************************************************/
void setupCLK(){
    SysCtlClockSet(SYSCTL_SYSDIV_4|SYSCTL_USE_PLL|SYSCTL_XTAL_16MHZ|SYSCTL_OSC_MAIN);
}
/*******************************
 * Enabling System Peripherals
 * PORTF and PORTD in this case
 ******************************/
void peripheralEnable(){
    SysCtlPeripheralEnable(SYSCTL_PERIPH_GPIOF);
    SysCtlPeripheralEnable(SYSCTL_PERIPH_GPIOD);
}
/************************************************
 * Configuring LCD Pins as Output
 * The pins PD7 and PF0 is locked. So they
   have to be unlocked before using it as an
   output pin.
 ***********************************************/
void configIOPin(){
    HWREG(GPIO_PORTD_BASE + GPIO_O_LOCK) = GPIO_LOCK_KEY; //getting the key
    HWREG(GPIO_PORTD_BASE + GPIO_O_CR) |= (1<<7);   //Unlocking the pin
    HWREG(GPIO_PORTD_BASE + GPIO_O_LOCK) = 0;   //Relocking the pin

    HWREG(GPIO_PORTF_BASE + GPIO_O_LOCK) = GPIO_LOCK_KEY;   //getting the key
    HWREG(GPIO_PORTF_BASE + GPIO_O_CR) |= 0x01;     //unlocking the pin
    HWREG(GPIO_PORTF_BASE + GPIO_O_LOCK) = 0;       //relocking the pin
    GPIOPinTypeGPIOOutput(lcdPORT,EN|RS);
    GPIOPinTypeGPIOOutput(lcdDDR,D4|D5|D6|D7);
}
/******************************************
 * This function is used to initialize LCD
 * The LCD is operated in 4 bit mode
 * It is also set in auto increment mode
 *****************************************/
void lcdInit(){
    lcdCommand(0x28);
    /**************************
    0x30 8bit mode single line*
    0x38 8bit mode double line*
    0x20 4bit mode single line*
    0x28 4bit mode double line*
    ***************************/
    lcdCommand(0x06);//entry mode and auto increment mode
    lcdCommand(0x0F);
    /********************************
    Display off Cursor off      0x08*
    Display on Cursor on        0x0E*
    Display on Cursor off       0x0C*
    Display on Cursor blinking  0x0F*
    *********************************/
}
***************************************************************************************
 * This function is used to send commands to LCD
 * The first 4 bits are sent first and then the last 4 bits
 * The bits are shifted left and right appropriately to fit in last 4 bits of port D
 ***************************************************************************************/
void lcdCommand(unsigned char command){
    GPIOPinWrite(lcdPORT,RS|EN,0);
    GPIOPinWrite(lcdDDR,D4|D5|D6|D7,0);
    _delay_us(100);
    GPIOPinWrite(lcdDDR,D4|D5|D6|D7,command);   //Putting first 4 bits in data lines of LCD
    _delay_us(100);
    GPIOPinWrite(lcdPORT,EN|RS,0x04);   //setting enable pin for a period of 1ms
    _delay_ms(1);
    GPIOPinWrite(lcdPORT,EN,0);
    _delay_us(100);
    GPIOPinWrite(lcdDDR,D4|D5|D6|D7,(command<<4));  //Putting last 4 bits in data lines of LCD
    _delay_ms(1);
    GPIOPinWrite(lcdPORT,EN|RS,0x04);   //setting enable pin for a period of 1ms
    _delay_ms(1);
    GPIOPinWrite(lcdPORT,EN,0);
    _delay_us(100);
}
***************************************************************************************
 * This function is used to send data to LCD
 * The first 4 bits are sent first and then the last 4 bits
 * The bits are shifted left and right appropriately to fit in last 4 bits of port A
 ***************************************************************************************/
void lcdData(unsigned char data){
    lcdCheck();
    GPIOPinWrite(lcdPORT,RS|EN,0);
    GPIOPinWrite(lcdDDR,D4|D5|D6|D7,0);
    GPIOPinWrite(lcdDDR,D4|D5|D6|D7,data);  //Putting first 4 bits in data lines of LCD
    _delay_us(100);
    GPIOPinWrite(lcdPORT,EN|RS,0x05);   //setting enable pin for a period of 1ms
    _delay_ms(1);                       //Setting the RS pin
    GPIOPinWrite(lcdPORT,EN,0);
    _delay_us(100);
    GPIOPinWrite(lcdDDR,D4|D5|D6|D7,(data<<4));     //Putting last 4 bits in data lines of LCD
    _delay_us(100);
    GPIOPinWrite(lcdPORT,EN|RS,0x05);   //setting enable pin for a period of 1ms
    _delay_ms(1);                       //Setting the RS pin
    GPIOPinWrite(lcdPORT,EN,0);
    cursorPositionCheck=(cursorPositionCheck+1)%32;
}
/************************************************
 * This function is used to send strings to LCD
 ***********************************************/
void lcdString(char* string){
    unsigned char i=0;
    while(string[i])
        lcdData(string[i++]);
}
/***********************************************************
 * This function is used to position of the cursor on LCD
 **********************************************************/
void lcdGotoxy(unsigned char x,unsigned char y)
{
    cursorPositionCheck=y*16+x;
    lcdCommand(0x80+x+(64*y));
}
/************************************************
 * This function is used to clear the LCD
 ***********************************************/
void lcdClear(){
    cursorPositionCheck=0;
    lcdCommand(0x01);
    _delay_ms(3);
}
******************************************************************
 * This function is used to check the position of cursor on LCD
 *****************************************************************/
void lcdCheck(){
    if(cursorPositionCheck==16)
    lcdGotoxy(0,1);
    else if(cursorPositionCheck==0)
    lcdGotoxy(0,0);
}
/*************************************
 * Calculating Delays
 *************************************/
void _delay_ms(uint64_t delay){
    SysCtlDelay(delay*(SysCtlClockGet()/3000));
}
void _delay_us(uint64_t delay){
    SysCtlDelay(delay*(SysCtlClockGet()/3000000UL));
}

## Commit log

2017-05-24 lab 0
2017-05-24 lab 1
2017-05-25 Lab-2
2017-05-27 lab 4
2017-05-27 lab 3
2017-05-29 lcd Codes
2017-05-30 29th Of May
2017-05-30 Daughter Board footprint library file
2017-05-30 Included Special Pins Of TM4C123Gh6PM in the sheet
2017-05-31 level converter using BJT
2017-05-31 Wired And Wireless Serial Communication Achieved
2017-05-31 Level Convertor Schematics using Diodes
2017-05-31 2 Way Wireless Communication
2017-05-31 ADC interfacing with IR
2017-05-31 ADC full project
2017-05-31 Started Schematics
2017-05-31 Power Supply Updated
2017-06-01 Excel Sheet updated
2017-06-01 sample
2017-06-01 Work Continues
2017-06-02 Schematic Almost Complete
2017-06-03 Pin details for schematic with pulgable TIVA board
2017-06-03 Schematic for Plugable daughter Board
2017-06-05 Schematic updated
2017-06-05 Schematic-2 Final
2017-06-05 Progress Presentation I
2017-06-06 Final changes to Schematic 2
2017-06-07 Port Expander Added
2017-06-07 Layout of daughter board
2017-06-08 Final schematic of TIVA Plugable Daughter Board on 8-6-2017
2017-06-08 Final tweaks to plugable Tiva board
2017-06-09 Layout
2017-06-09 Plugable tiva
2017-06-09 Layout of plugabe tiva
2017-06-09 uC based Board with manual Routing
2017-06-09 Plugable TIVA board at 17:46
2017-06-10 Interrupt of Port Expander Added
2017-06-10 Plugable TIVA changes on 10-6-2017
2017-06-10 Plugable Tiva board changes at 14:26 on 10-06-2017
2017-06-12 Adding groung to layout of plugable TIVA board
2017-06-13 Layout Complete
2017-06-13 Manual Started
2017-06-13 Plugable TIVA changes on 13-06-17
2017-06-13 final
2017-06-13 Documentation Started
2017-06-14 Schematics for documentation
2017-06-14 Manual
2017-06-14 Schematics for manual
2017-06-14 Made progress in Documentation
2017-06-16 Manual Updated
2017-06-16 Manual hardware part in progress
2017-06-16 updated To Do list
2017-06-16 Powering and reset switch circuit added to manual
2017-06-16 Schematic of LCD for manual
2017-06-17 Properly Documented Codes
2017-06-17 Updated Hardware manual and Sensor list
2017-06-17 PWM code
2017-06-17 17/6/2017
2017-06-19 Codes
2017-06-19 Codes for velocity control
2017-06-19 Servo motor interfacing code. This code is not tested due to unavailabiity of servo motors
2017-06-19 Timer interrupt Overflow code
2017-06-20 Demo
2017-06-21 LCD untested code
2017-06-22 6 22
2017-06-23 sample commit
2017-06-23 commit for merging
2017-06-23 Documented Timer overflow code, ADC code
2017-06-23 Documented code for ADC
2017-06-23 LCD and ADC code for uC based board
2017-06-26 Message
2017-06-26 Software Manual
2017-06-27 27/6
2017-06-27 Report
2017-06-27 TIVA based Daughter Manual Board First Draft
2017-06-27 Poster for Exhibition
2017-06-28 Servo code working
2017-06-28 Poster completed
2017-06-28 Final poster design
2017-06-28 Sharp sensor Interfaced
2017-06-28 poster final modification
2017-06-29 Poster final changes
2017-06-29 Poster changes
2017-06-29 6/29
2017-06-29 LCD code changes
2017-06-29 Line Follower code and Updated Daughter Board Manual
2017-07-04 Version 2 of Plug and Play Board
2017-07-04 Updated Software Manual
2017-07-06 Orgainising
2017-07-06 Organising
2017-07-07 Changes is software manual and commented code for LCD
2017-07-08 Hardware Manual
